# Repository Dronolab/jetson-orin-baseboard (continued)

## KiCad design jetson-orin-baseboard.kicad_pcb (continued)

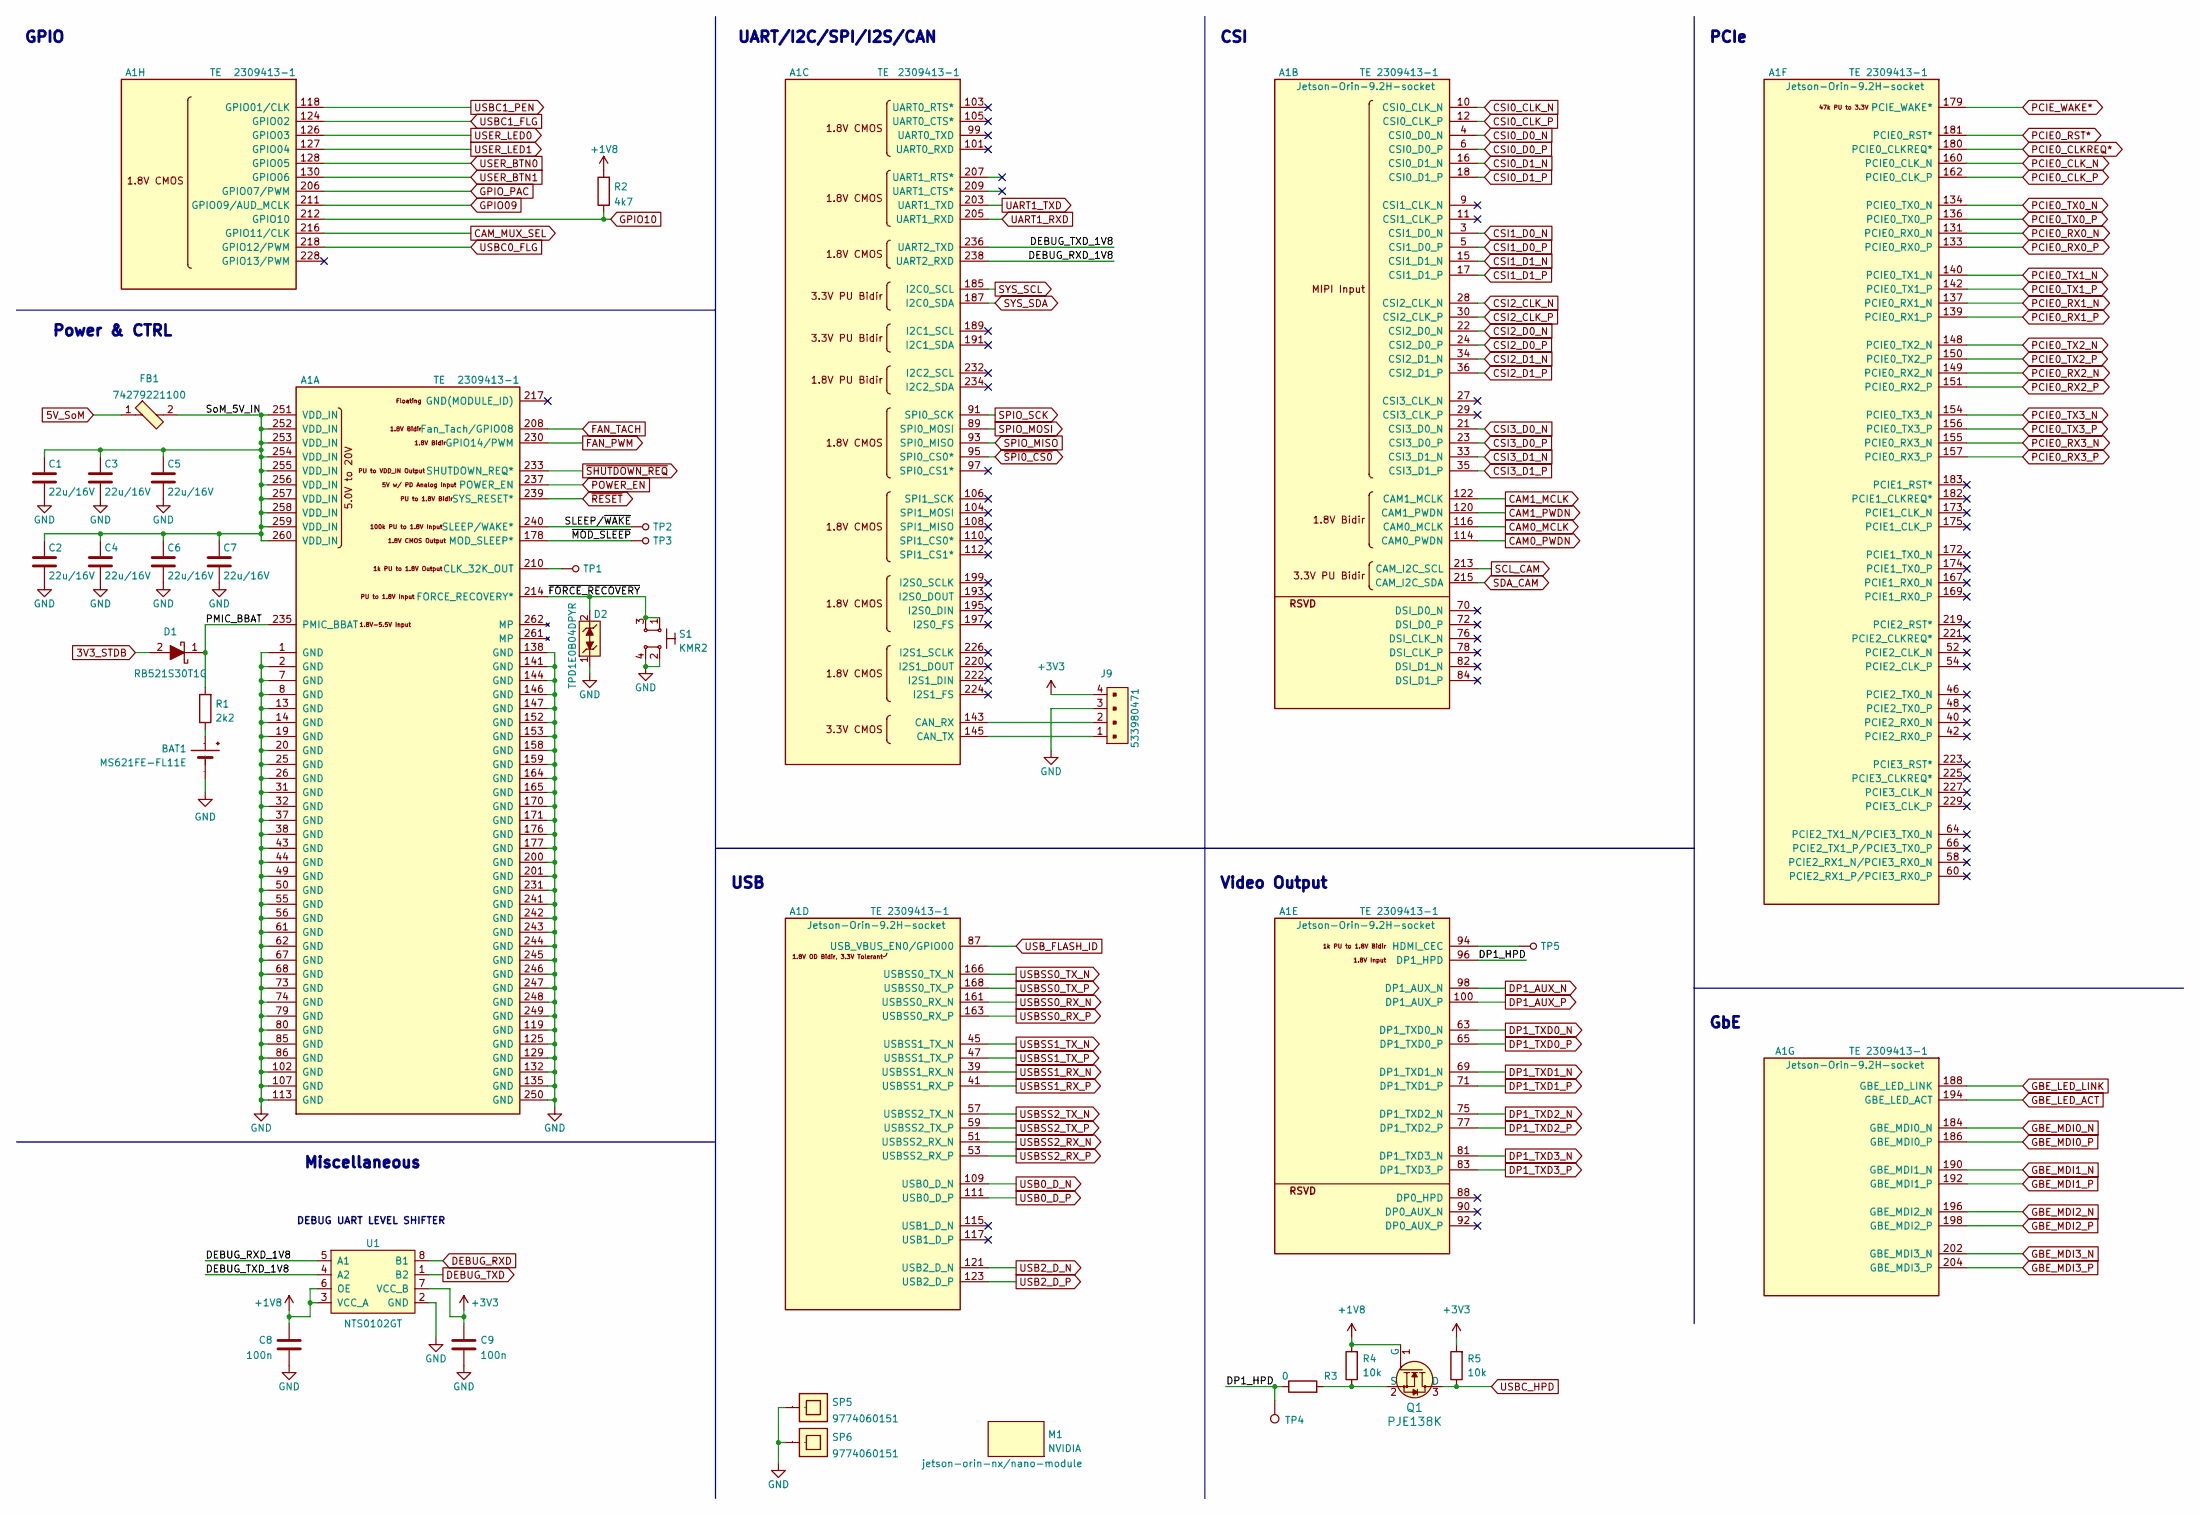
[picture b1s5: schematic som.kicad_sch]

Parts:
A1: Jetson-Orin-9.2H-socket; TE_2309413; MPN 2309413-1
BAT1: MS621FE-FL11E; MPN MS621FE-FL11E
C1, C2, C3, C4, C5, C6, C7: C_22u_0603_16V; 0603-cap; MPN CL10A226MO7JZNC
C8, C9: C_100n_0402; 0402-cap; MPN GRM155R61H104KE14D
D1: RB521S30T1G; SOD-523; MPN RB521S30T1G
D2: TPD1E0B04DPYR; XDFN-2_1x0.60mm; MPN TPD1E0B04DPYR
FB1: 74279221100; 1206-res; MPN 74279221100
J9: 533980471; Molex_PicoBlade_53398-0471_1x04-1MP_P1.25mm_Vertical; MPN 0533980471
M1: jetson-orin-nx/nano-module; jetson-orin-nx-nano-module
Q1: PJE138K; SOT-523; MPN PJE138K_R1_00001
R1: R_2k2_0402; 0402-res; MPN RC0402FR-072K2L
R2: R_4k7_0402; 0402-res; MPN MCS04020C4701FE000
R3: 0; 0402-res
R4, R5: 10k; 0402-res
S1: KMR2; SW_SPST_4.2x2.8; MPN KMR211NGLFS
SP5, SP6: 9774060151; MPN 9774060151
TP1, TP2, TP3, TP5: TP_SMD_0_75MM; Testpoint_smd_0_75mm
TP4: TestPoint; Testpoint_smd_0_75mm
U1: NTS0102GT; PSON50P100X195X50-8N; MPN NTS0102GT

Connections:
3V3_STDB: D1.2; also elsewhere on the board
5V_SoM: FB1.1; also elsewhere on the board
+1V8: C8.2, Q1.1 (G), R2.2, R4.2, U1.3 (VCC_A), U1.6 (OE); also elsewhere on the board
/SoM/DEBUG_RXD_1V8: A1.238 (UART2_RXD), U1.5 (A1)
/SoM/DEBUG_TXD_1V8: A1.236 (UART2_TXD), U1.4 (A2)
/SoM/DP1_HPD: A1.96 (DP1_HPD), R3.1, TP4.1
/SoM/PMIC_BBAT: A1.235 (PMIC_BBAT), D1.1, R1.2
/SoM/SLEEP/~WAKE: A1.240 (SLEEP/WAKE*), TP2.1
/SoM/SoM_5V_IN: A1.251 (VDD_IN), A1.252 (VDD_IN), A1.253 (VDD_IN), A1.254 (VDD_IN), A1.255 (VDD_IN), A1.256 (VDD_IN), A1.257 (VDD_IN), A1.258 (VDD_IN), A1.259 (VDD_IN), A1.260 (VDD_IN), C1.1, C2.1, C3.1, C4.1, C5.1, C6.1, C7.1, FB1.2
/SoM/~FORCE_RECOVERY: A1.214 (FORCE_RECOVERY*), D2.2, S1.1, S1.3
/SoM/~MOD_SLEEP: A1.178 (MOD_SLEEP*), TP3.1
CAM0_MCLK: A1.116 (CAM0_MCLK); also elsewhere on the board
CAM0_PWDN: A1.114 (CAM0_PWDN); also elsewhere on the board
CAM1_MCLK: A1.122 (CAM1_MCLK); also elsewhere on the board
CAM1_PWDN: A1.120 (CAM1_PWDN); also elsewhere on the board
CAM_MUX_SEL: A1.216 (GPIO11/CLK); also elsewhere on the board
CSI0_CLK_N: A1.10 (CSI0_CLK_N); also elsewhere on the board
CSI0_CLK_P: A1.12 (CSI0_CLK_P); also elsewhere on the board
CSI0_D0_N: A1.4 (CSI0_D0_N); also elsewhere on the board
CSI0_D0_P: A1.6 (CSI0_D0_P); also elsewhere on the board
CSI0_D1_N: A1.16 (CSI0_D1_N); also elsewhere on the board
CSI0_D1_P: A1.18 (CSI0_D1_P); also elsewhere on the board
CSI1_D0_N: A1.3 (CSI1_D0_N); also elsewhere on the board
CSI1_D0_P: A1.5 (CSI1_D0_P); also elsewhere on the board
CSI1_D1_N: A1.15 (CSI1_D1_N); also elsewhere on the board
CSI1_D1_P: A1.17 (CSI1_D1_P); also elsewhere on the board
CSI2_CLK_N: A1.28 (CSI2_CLK_N); also elsewhere on the board
CSI2_CLK_P: A1.30 (CSI2_CLK_P); also elsewhere on the board
CSI2_D0_N: A1.22 (CSI2_D0_N); also elsewhere on the board
CSI2_D0_P: A1.24 (CSI2_D0_P); also elsewhere on the board
CSI2_D1_N: A1.34 (CSI2_D1_N); also elsewhere on the board
CSI2_D1_P: A1.36 (CSI2_D1_P); also elsewhere on the board
CSI3_D0_N: A1.21 (CSI3_D0_N); also elsewhere on the board
CSI3_D0_P: A1.23 (CSI3_D0_P); also elsewhere on the board
CSI3_D1_N: A1.33 (CSI3_D1_N); also elsewhere on the board
CSI3_D1_P: A1.35 (CSI3_D1_P); also elsewhere on the board
DEBUG_RXD: U1.8 (B1); also elsewhere on the board
DEBUG_TXD: U1.1 (B2); also elsewhere on the board
DP1_AUX_N: A1.98 (DP1_AUX_N); also elsewhere on the board
DP1_AUX_P: A1.100 (DP1_AUX_P); also elsewhere on the board
DP1_TXD0_N: A1.63 (DP1_TXD0_N); also elsewhere on the board
DP1_TXD0_P: A1.65 (DP1_TXD0_P); also elsewhere on the board
DP1_TXD1_N: A1.69 (DP1_TXD1_N); also elsewhere on the board
DP1_TXD1_P: A1.71 (DP1_TXD1_P); also elsewhere on the board
DP1_TXD2_N: A1.75 (DP1_TXD2_N); also elsewhere on the board
DP1_TXD2_P: A1.77 (DP1_TXD2_P); also elsewhere on the board
DP1_TXD3_P: A1.83 (DP1_TXD3_P); also elsewhere on the board
FAN_PWM: A1.230 (GPIO14/PWM); also elsewhere on the board
FAN_TACH: A1.208 (Fan_Tach/GPIO08); also elsewhere on the board
GBE_LED_ACT: A1.194 (GBE_LED_ACT); also elsewhere on the board
GBE_LED_LINK: A1.188 (GBE_LED_LINK); also elsewhere on the board
GBE_MDI0_N: A1.184 (GBE_MDI0_N); also elsewhere on the board
GBE_MDI0_P: A1.186 (GBE_MDI0_P); also elsewhere on the board
GBE_MDI1_N: A1.190 (GBE_MDI1_N); also elsewhere on the board
GBE_MDI1_P: A1.192 (GBE_MDI1_P); also elsewhere on the board
GBE_MDI2_N: A1.196 (GBE_MDI2_N); also elsewhere on the board
GBE_MDI2_P: A1.198 (GBE_MDI2_P); also elsewhere on the board
GBE_MDI3_N: A1.202 (GBE_MDI3_N); also elsewhere on the board
GBE_MDI3_P: A1.204 (GBE_MDI3_P); also elsewhere on the board
GPIO09: A1.211 (GPIO09/AUD_MCLK); also elsewhere on the board
GPIO10: A1.212 (GPIO10), R2.1; also elsewhere on the board
unnamed: A1.210 (CLK_32K_OUT), TP1.1
unnamed: A1.94 (HDMI_CEC), TP5.1
unnamed: BAT1.+, R1.1
unnamed: Q1.2 (S), R3.2, R4.1
PCIE0_CLKREQ*: A1.180 (PCIE0_CLKREQ*); also elsewhere on the board
PCIE0_CLK_N: A1.160 (PCIE0_CLK_N); also elsewhere on the board
PCIE0_CLK_P: A1.162 (PCIE0_CLK_P); also elsewhere on the board
PCIE0_RST*: A1.181 (PCIE0_RST*); also elsewhere on the board
PCIE0_RX0_N: A1.131 (PCIE0_RX0_N); also elsewhere on the board
PCIE0_RX0_P: A1.133 (PCIE0_RX0_P); also elsewhere on the board
PCIE0_RX1_N: A1.137 (PCIE0_RX1_N); also elsewhere on the board
PCIE0_RX1_P: A1.139 (PCIE0_RX1_P); also elsewhere on the board
PCIE0_RX2_N: A1.149 (PCIE0_RX2_N); also elsewhere on the board
PCIE0_RX2_P: A1.151 (PCIE0_RX2_P); also elsewhere on the board
PCIE0_RX3_N: A1.155 (PCIE0_RX3_N); also elsewhere on the board
PCIE0_RX3_P: A1.157 (PCIE0_RX3_P); also elsewhere on the board
PCIE0_TX0_N: A1.134 (PCIE0_TX0_N); also elsewhere on the board
PCIE0_TX0_P: A1.136 (PCIE0_TX0_P); also elsewhere on the board
PCIE0_TX1_N: A1.140 (PCIE0_TX1_N); also elsewhere on the board
PCIE0_TX1_P: A1.142 (PCIE0_TX1_P); also elsewhere on the board
PCIE0_TX2_N: A1.148 (PCIE0_TX2_N); also elsewhere on the board
PCIE0_TX2_P: A1.150 (PCIE0_TX2_P); also elsewhere on the board
PCIE0_TX3_N: A1.154 (PCIE0_TX3_N); also elsewhere on the board
PCIE0_TX3_P: A1.156 (PCIE0_TX3_P); also elsewhere on the board
PCIE_WAKE*: A1.179 (PCIE_WAKE*); also elsewhere on the board
POWER_EN: A1.237 (POWER_EN); also elsewhere on the board
SCL_CAM: A1.213 (CAM_I2C_SCL); also elsewhere on the board
SDA_CAM: A1.215 (CAM_I2C_SDA); also elsewhere on the board
SPIO_MISO: A1.93 (SPI0_MISO); also elsewhere on the board
SPIO_MOSI: A1.89 (SPI0_MOSI); also elsewhere on the board
SPIO_SCK: A1.91 (SPI0_SCK); also elsewhere on the board
SYS_SCL: A1.185 (I2C0_SCL); also elsewhere on the board
SYS_SDA: A1.187 (I2C0_SDA); also elsewhere on the board
USB0_D_N: A1.109 (USB0_D_N); also elsewhere on the board
USB0_D_P: A1.111 (USB0_D_P); also elsewhere on the board
USB2_D_N: A1.121 (USB2_D_N); also elsewhere on the board
USB2_D_P: A1.123 (USB2_D_P); also elsewhere on the board
USBC0_FLG: A1.218 (GPIO12/PWM); also elsewhere on the board
USBC1_FLG: A1.124 (GPIO02); also elsewhere on the board
USBC1_PEN: A1.118 (GPIO01/CLK); also elsewhere on the board
USBC_HPD: Q1.3 (D), R5.1; also elsewhere on the board
USBSS0_RX_N: A1.161 (USBSS0_RX_N); also elsewhere on the board
USBSS0_RX_P: A1.163 (USBSS0_RX_P); also elsewhere on the board
USBSS0_TX_N: A1.166 (USBSS0_TX_N); also elsewhere on the board
USBSS0_TX_P: A1.168 (USBSS0_TX_P); also elsewhere on the board
USBSS1_RX_N: A1.39 (USBSS1_RX_N); also elsewhere on the board
USBSS1_RX_P: A1.41 (USBSS1_RX_P); also elsewhere on the board
USBSS1_TX_N: A1.45 (USBSS1_TX_N); also elsewhere on the board
USBSS1_TX_P: A1.47 (USBSS1_TX_P); also elsewhere on the board
USBSS2_RX_N: A1.51 (USBSS2_RX_N); also elsewhere on the board
USBSS2_RX_P: A1.53 (USBSS2_RX_P); also elsewhere on the board
USBSS2_TX_N: A1.57 (USBSS2_TX_N); also elsewhere on the board
USBSS2_TX_P: A1.59 (USBSS2_TX_P); also elsewhere on the board
USB_FLASH_ID: A1.87 (USB_VBUS_EN0/GPIO00); also elsewhere on the board
USER_BTN0: A1.128 (GPIO05); also elsewhere on the board
USER_BTN1: A1.130 (GPIO06); also elsewhere on the board
USER_LED0: A1.126 (GPIO03); also elsewhere on the board
USER_LED1: A1.127 (GPIO04); also elsewhere on the board
~RESET: A1.239 (SYS_RESET*); also elsewhere on the board
~SHUTDOWN_REQ: A1.233 (SHUTDOWN_REQ*); also elsewhere on the board
~SPI0_CS0: A1.95 (SPI0_CS0*); also elsewhere on the board

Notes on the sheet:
DEBUG UART LEVEL SHIFTER
CSI
Video Output
Power & CTRL
UART/I2C/SPI/I2S/CAN
PCIe
GbE
USB
GPIO
Miscellaneous

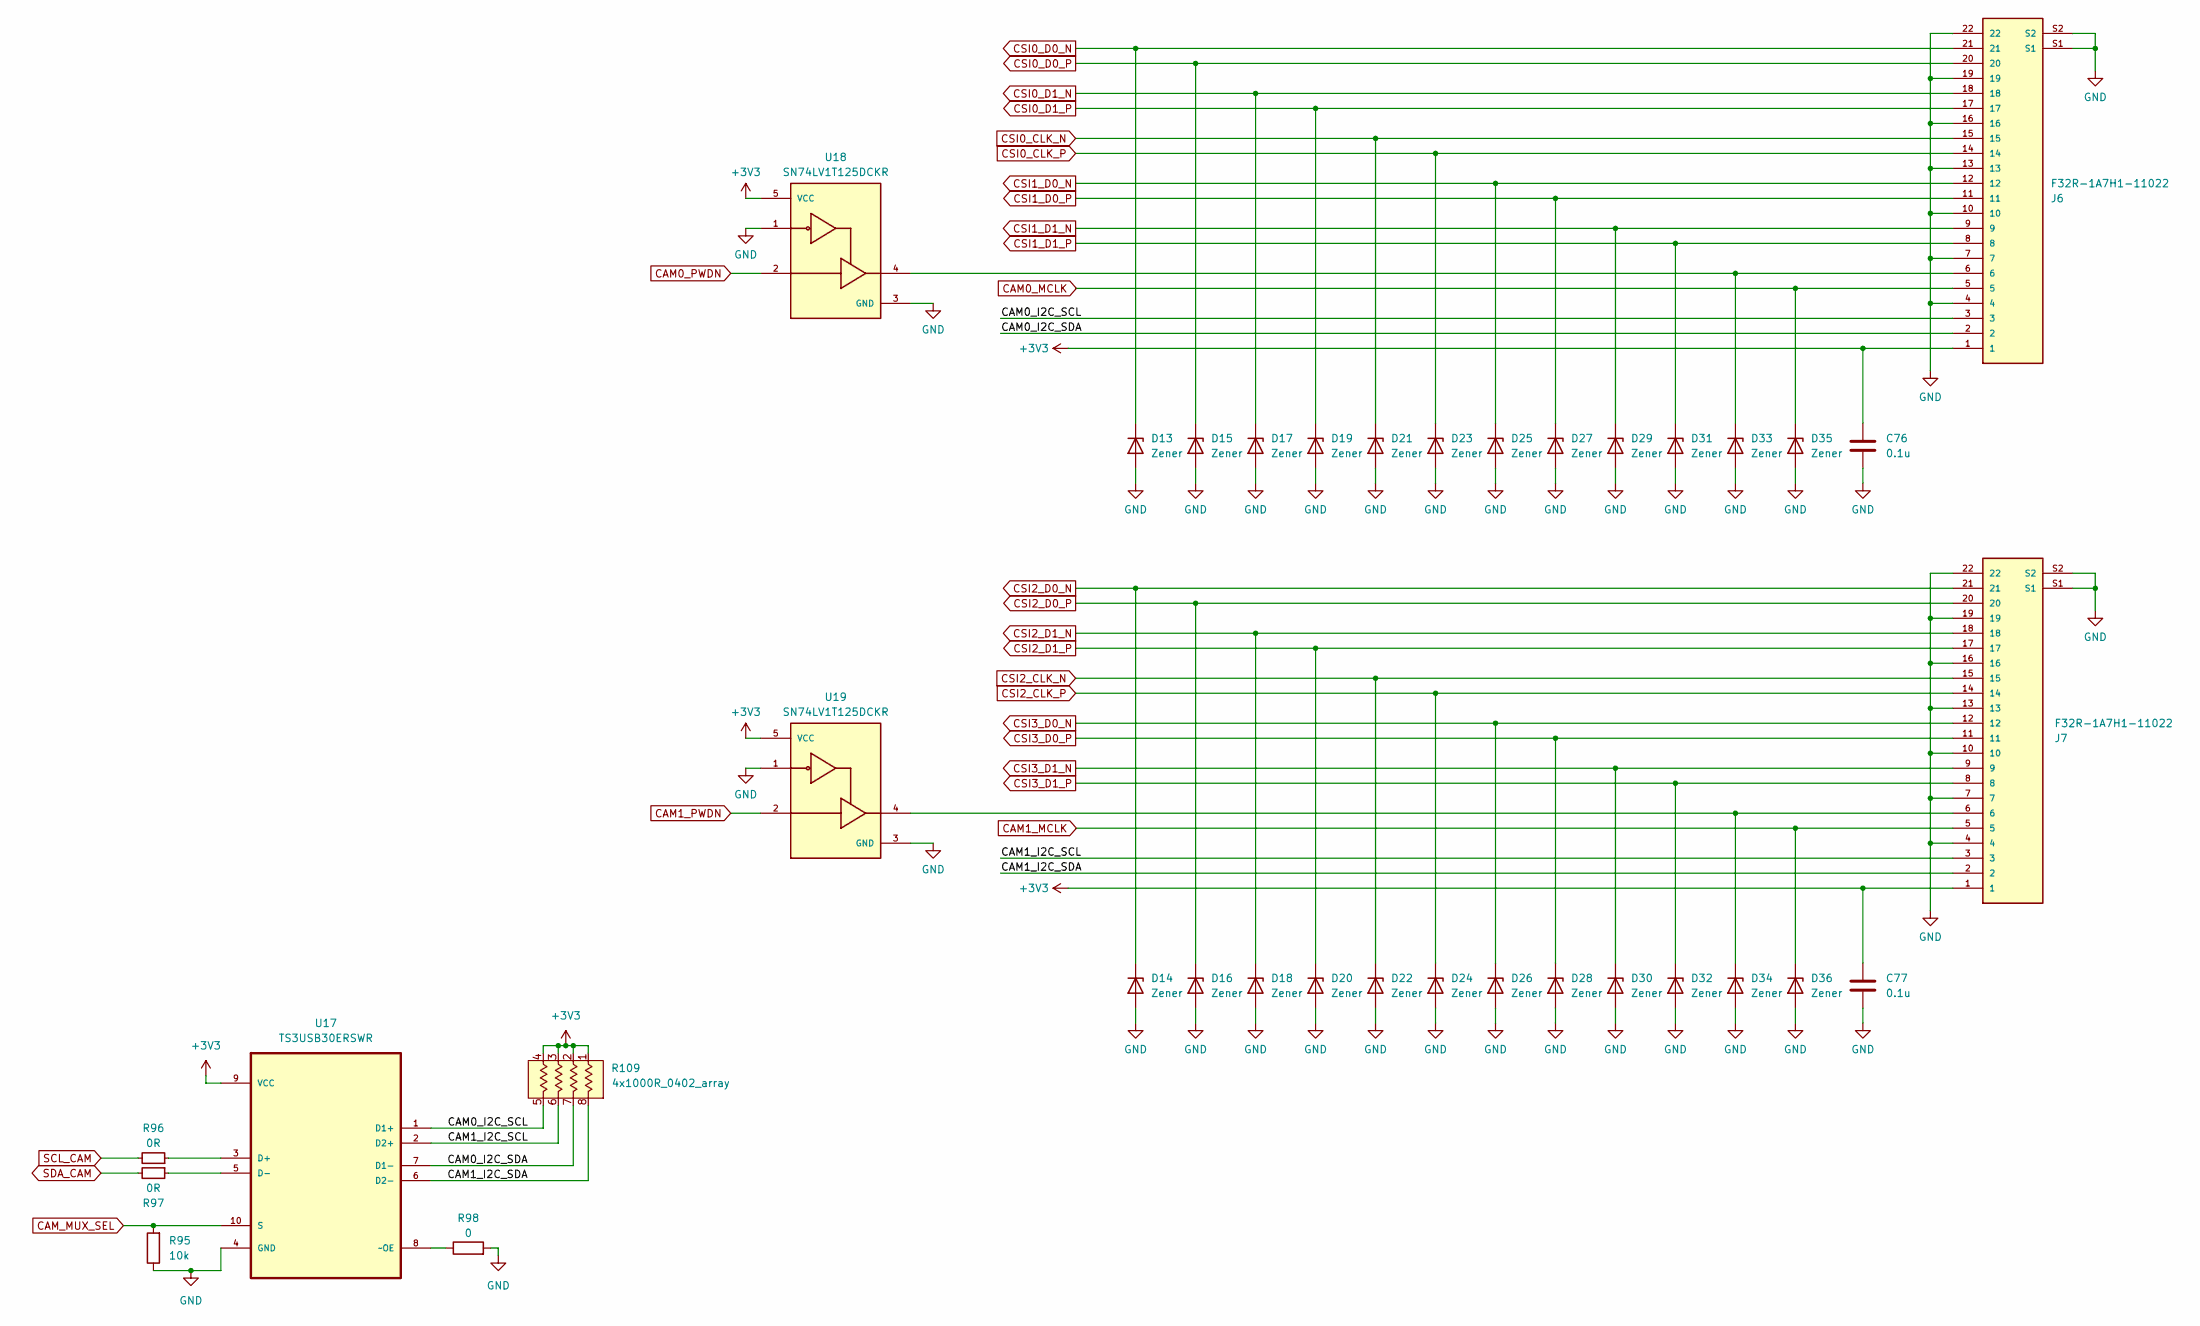
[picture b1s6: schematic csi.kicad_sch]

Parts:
C76, C77: 0.1u; 0402-cap
D13, D14, D15, D16, D17, D18, D19, D20, D21, D22, D23, D24, D25, D26, D27, D28, D29, D30, D31, D32, D33, D34, D35, D36: Zener; DFN1006-2
J6, J7: F32R-1A7H1-11022; AMPHENOL_F32R-1A7H1-11022; PARTREV C
R95: 10k; 0402-res
R96, R97: R_0R_0402; 0402-res; MPN ERJ2GE0R00X
R98: 0; 0402-res
R109: 4x1000R_0402_array; R_Array_4x0402; MPN EXB-28V331JX
U17: TS3USB30ERSWR; QFN40P140X180X55-10N; MPN TS3USB30ERSWR
U18, U19: SN74LV1T125DCKR; SOT65P210X110-5N; PARTREV A

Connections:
/Cameras/CAM1_I2C_SDA: J7.2, R109.8, U17.6 (D2-); also elsewhere on the board
CAM0_MCLK: D35.K, J6.5; also elsewhere on the board
CAM0_PWDN: U18.2; also elsewhere on the board
CAM1_MCLK: D36.K, J7.5; also elsewhere on the board
CAM1_PWDN: U19.2; also elsewhere on the board
CAM_MUX_SEL: R95.2, U17.10 (S); also elsewhere on the board
CSI0_CLK_N: D21.K, J6.15; also elsewhere on the board
CSI0_CLK_P: D23.K, J6.14; also elsewhere on the board
CSI0_D0_N: D13.K, J6.21; also elsewhere on the board
CSI0_D0_P: D15.K, J6.20; also elsewhere on the board
CSI0_D1_N: D17.K, J6.18; also elsewhere on the board
CSI0_D1_P: D19.K, J6.17; also elsewhere on the board
CSI1_D0_N: D25.K, J6.12; also elsewhere on the board
CSI1_D0_P: D27.K, J6.11; also elsewhere on the board
CSI1_D1_N: D29.K, J6.9; also elsewhere on the board
CSI1_D1_P: D31.K, J6.8; also elsewhere on the board
CSI2_CLK_N: D22.K, J7.15; also elsewhere on the board
CSI2_CLK_P: D24.K, J7.14; also elsewhere on the board
CSI2_D0_N: D14.K, J7.21; also elsewhere on the board
CSI2_D0_P: D16.K, J7.20; also elsewhere on the board
CSI2_D1_N: D18.K, J7.18; also elsewhere on the board
CSI2_D1_P: D20.K, J7.17; also elsewhere on the board
CSI3_D0_N: D26.K, J7.12; also elsewhere on the board
CSI3_D0_P: D28.K, J7.11; also elsewhere on the board
CSI3_D1_N: D30.K, J7.9; also elsewhere on the board
CSI3_D1_P: D32.K, J7.8; also elsewhere on the board
unnamed: D33.K, J6.6, U18.4
unnamed: D34.K, J7.6, U19.4
unnamed: R96.1, U17.3 (D+)
unnamed: R97.1, U17.5 (D-)
unnamed: R98.1, U17.8 (~OE)
SCL_CAM: R96.2; also elsewhere on the board
SDA_CAM: R97.2; also elsewhere on the board

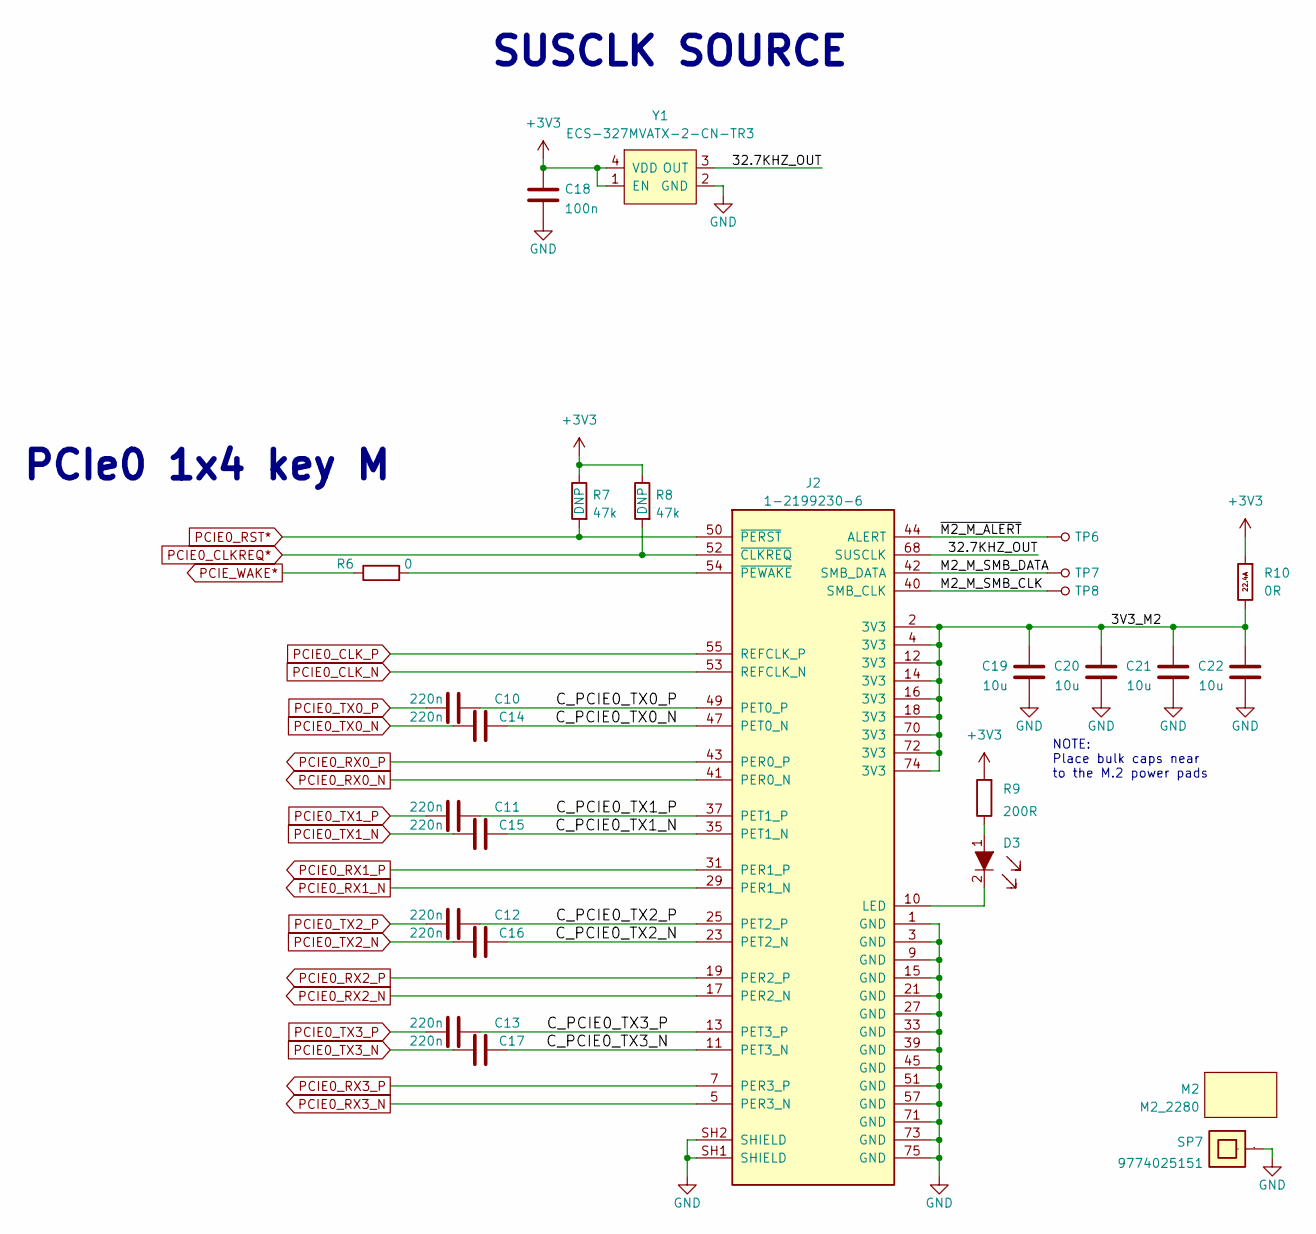
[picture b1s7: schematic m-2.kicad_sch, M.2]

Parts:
C10, C11, C12, C13, C14, C15, C16, C17: C_220n_0402; 0402-cap; MPN CC0402KRX5R6BB224
C18: C_100n_0402; 0402-cap; MPN GRM155R61H104KE14D
C19, C20, C21, C22: C_10u_0603; 0603-cap; MPN GRM188R61A106KE69D
D3: LTST-C190GKT; LED_0603; MPN LTST-C190GKT
J2: 1-2199230-6; MPN 1-2199230-6
M2: M2_2280; m2_2280
R6: 0; 0402-res
R7, R8: R_47k_0402; 0402-res; MPN MCMR04X4702FTL
R9: R_200R_0402; 0402-res; MPN RC0402FR-07200RL
R10: R_0R_0603_HPWR; 0603-res; MPN PMR03EZPJ000
SP7: 9774025151; MPN 9774025151
TP6, TP7, TP8: TP_SMD_0_75MM; Testpoint_smd_0_75mm
Y1: ECS-327MVATX-2-CN-TR3; Oscillator_SMD_ECS_2520MV-xxx-xx-4Pin_2.5x2.0mm; MPN ECS-327MVATX-2-CN-TR3

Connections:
/M.2/3V3_M2: C19.1, C20.1, C21.1, C22.1, J2.2 (3V3), J2.4 (3V3), J2.12 (3V3), J2.14 (3V3), J2.16 (3V3), J2.18 (3V3), J2.70 (3V3), J2.72 (3V3), J2.74 (3V3), R10.1
/M.2/32.7KHZ_OUT: J2.68 (SUSCLK), Y1.3 (OUT)
/M.2/C_PCIE0_TX0_N: C14.2, J2.47 (PET0_N)
/M.2/C_PCIE0_TX0_P: C10.2, J2.49 (PET0_P)
/M.2/C_PCIE0_TX1_N: C15.2, J2.35 (PET1_N)
/M.2/C_PCIE0_TX1_P: C11.2, J2.37 (PET1_P)
/M.2/C_PCIE0_TX2_N: C16.2, J2.23 (PET2_N)
/M.2/C_PCIE0_TX2_P: C12.2, J2.25 (PET2_P)
/M.2/C_PCIE0_TX3_N: C17.2, J2.11 (PET3_N)
/M.2/C_PCIE0_TX3_P: C13.2, J2.13 (PET3_P)
/M.2/M2_M_SMB_CLK: J2.40 (SMB_CLK), TP8.1
/M.2/M2_M_SMB_DATA: J2.42 (SMB_DATA), TP7.1
/M.2/~M2_M_ALERT: J2.44 (ALERT), TP6.1
unnamed: D3.1, R9.1
unnamed: D3.2, J2.10 (LED)
unnamed: J2.54 (~PEWAKE), R6.2
PCIE0_CLKREQ*: J2.52 (~CLKREQ), R8.2; also elsewhere on the board
PCIE0_CLK_N: J2.53 (REFCLK_N); also elsewhere on the board
PCIE0_CLK_P: J2.55 (REFCLK_P); also elsewhere on the board
PCIE0_RST*: J2.50 (~PERST), R7.2; also elsewhere on the board
PCIE0_RX0_N: J2.41 (PER0_N); also elsewhere on the board
PCIE0_RX0_P: J2.43 (PER0_P); also elsewhere on the board
PCIE0_RX1_N: J2.29 (PER1_N); also elsewhere on the board
PCIE0_RX1_P: J2.31 (PER1_P); also elsewhere on the board
PCIE0_RX2_N: J2.17 (PER2_N); also elsewhere on the board
PCIE0_RX2_P: J2.19 (PER2_P); also elsewhere on the board
PCIE0_RX3_N: J2.5 (PER3_N); also elsewhere on the board
PCIE0_RX3_P: J2.7 (PER3_P); also elsewhere on the board
PCIE0_TX0_N: C14.1; also elsewhere on the board
PCIE0_TX0_P: C10.1; also elsewhere on the board
PCIE0_TX1_N: C15.1; also elsewhere on the board
PCIE0_TX1_P: C11.1; also elsewhere on the board
PCIE0_TX2_N: C16.1; also elsewhere on the board
PCIE0_TX2_P: C12.1; also elsewhere on the board
PCIE0_TX3_N: C17.1; also elsewhere on the board
PCIE0_TX3_P: C13.1; also elsewhere on the board
PCIE_WAKE*: R6.1; also elsewhere on the board

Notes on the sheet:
PCIe0 1x4 key M
NOTE: Place bulk caps near to the M.2 power pads
SUSCLK SOURCE

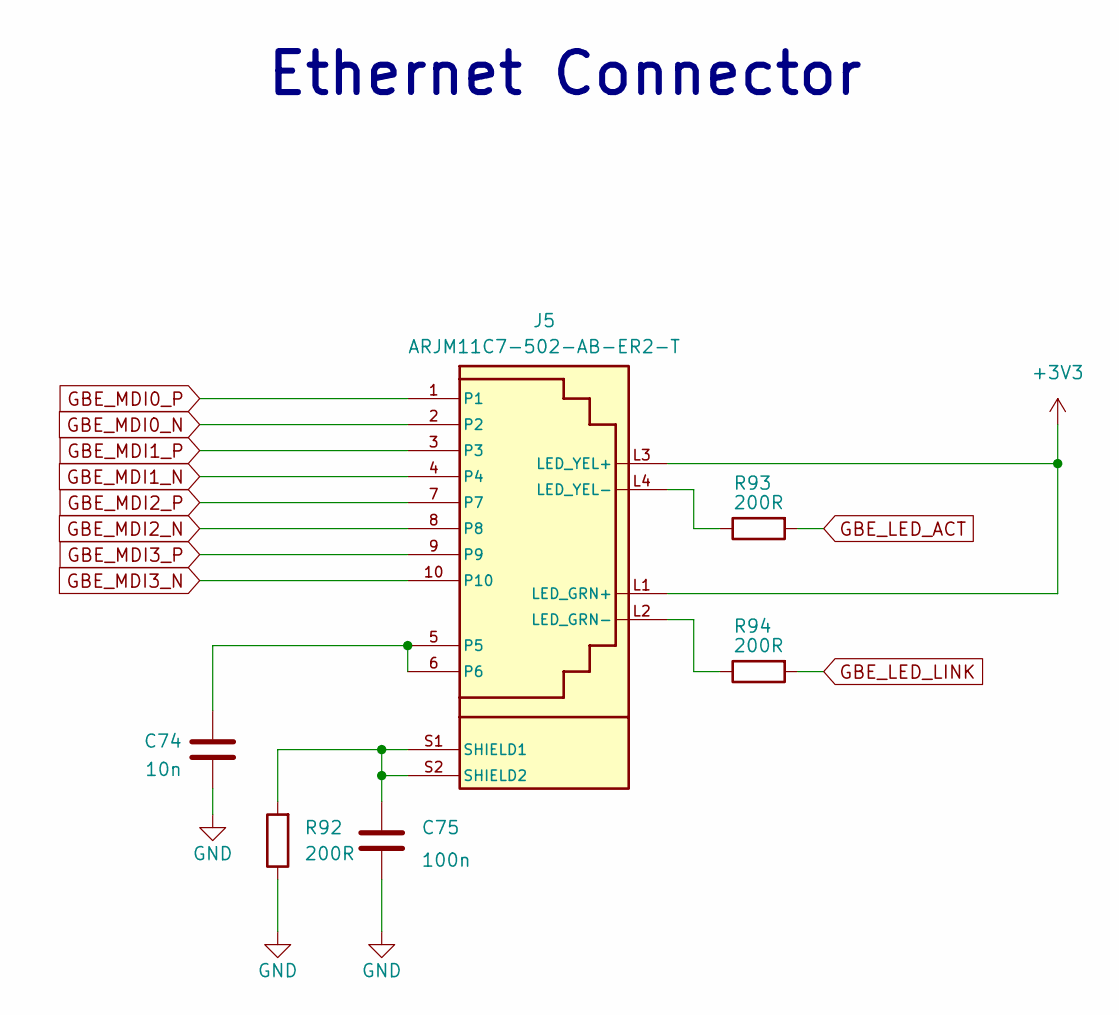
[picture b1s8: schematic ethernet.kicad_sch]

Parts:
C74: C_10n_0402; 0402-cap; MPN 04025G103ZAT2A
C75: C_100n_0402; 0402-cap; MPN GRM155R61H104KE14D
J5: ARJM11C7-502-AB-ER2-T; ABRACON_ARJM11C7-502-AB-ER2-T; MPN ARJM11C7-502-AB-ER2-T
R92, R93, R94: R_200R_0402; 0402-res; MPN RC0402FR-07200RL

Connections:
GBE_LED_ACT: R93.2; also elsewhere on the board
GBE_LED_LINK: R94.2; also elsewhere on the board
GBE_MDI0_N: J5.2; also elsewhere on the board
GBE_MDI0_P: J5.1; also elsewhere on the board
GBE_MDI1_N: J5.4; also elsewhere on the board
GBE_MDI1_P: J5.3; also elsewhere on the board
GBE_MDI2_N: J5.8; also elsewhere on the board
GBE_MDI2_P: J5.7; also elsewhere on the board
GBE_MDI3_N: J5.10; also elsewhere on the board
GBE_MDI3_P: J5.9; also elsewhere on the board
unnamed: J5.L2 (LED_GRN-), R94.1
unnamed: J5.L4 (LED_YEL-), R93.1
unnamed: C74.1, J5.5, J5.6
unnamed: C75.1, J5.S1 (SHIELD1), J5.S2 (SHIELD2), R92.2

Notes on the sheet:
Ethernet Connector

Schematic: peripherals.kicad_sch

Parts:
C78, C80: C_100n_0402; 0402-cap; MPN GRM155R61H104KE14D
C79: 0.1u; 0402-cap
C81: 2.2u; 0402-cap
C82: 10n; 0402-cap
C83: 0.47u; 0402-cap
C84, C85, C86, C88: C_1u_0402; 0402-cap; MPN C1005X6S1A105K050BC
C87, C89: 100n; 0402-cap
D37, D38: LTST-C190GKT; LED_0603; MPN LTST-C190GKT
D39, D40, D41, D42, D43, D44: TPD1E0B04DPYR; XDFN-2_1x0.60mm; MPN TPD1E0B04DPYR
J8: TC2050-IDC-NL; TC2050-IDC-NL_2x05_Vertical; MPN TC2050-IDC-NL
J9: 533980471; Molex_PicoBlade_53398-0471_1x04-1MP_P1.25mm_Vertical; MPN 0533980471
J10: 532611071; MOLEX_532611071; PARTREV J
J11: ERF8-020-05.0-S-DV-L-TR; SAMTEC_ERF8-020-05.0-S-DV-L-TR
Q4, Q5: PJE138K; SOT-523; MPN PJE138K_R1_00001
R103, R104, R117, R118: R_0R_0402; 0402-res; MPN ERJ2GE0R00X
R105: 4x0R_0201_array; EXB18V; MPN EXB-18VR000X
R106: 0; 0402-res
R107, R110: R_100k_0402; 0402-res; MPN CRCW0402100KFKEDHP
R108, R111: R_200R_0402; 0402-res; MPN RC0402FR-07200RL
R109: 4x330R_0402_array; R_Array_4x0402; MPN EXB-28V331JX
R112, R113: R_10k_0402; 0402-res; MPN CRCW040210K0FKEDHP
R114, R115, R116, R119: R_0R_0603; 0603-res; MPN CR0603-J/-000ELF
S2, S3: KMR2; SW_SPST_4.2x2.8; MPN KMR211NGLFS
U20: NTS0102GT; PSON50P100X195X50-8N; MPN NTS0102GT
U21: ICM-20602; LGA-16_3x3mm_P0.5mm_LayoutBorder3x5y

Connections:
+1V8: C78.2, C79.1, C81.1, R112.2, R113.2, R115.2, U20.3 (VCC_A), U20.6 (OE), U21.16 (VDD); also elsewhere on the board
+12V: R119.1
/Cameras/CAM1_I2C_SDA: R109.8; also elsewhere on the board
/Peripherals/1V8_CONN: C85.1, J11.02, J11.04, R115.1
/Peripherals/3V3_CONN: C84.1, J11.33, J11.35, J11.37, R114.1
/Peripherals/5V_CONN: C86.1, J11.01, J11.03, J11.05, J11.07, R116.2
/Peripherals/12V_CONN: C88.1, J11.32, J11.34, J11.36, J11.38, R119.2
/Peripherals/FC_RX: J10.3, J11.16
/Peripherals/FC_TX: J10.2, J11.14
/Peripherals/IO1: J10.5, J11.13
/Peripherals/IO2: J10.6, J11.11
/Peripherals/IO3: J10.7, J11.15
/Peripherals/IO4: J10.9, J11.08
/Peripherals/IO5: J10.10, J11.10
/Peripherals/USBSS1_TX_N_CONN: C89.1, D44.1, J11.22
/Peripherals/USBSS1_TX_P_CONN: C87.1, D43.1, J11.20
EEPROM_PWR: J8.1; also elsewhere on the board
FAN_PWM: U20.5 (A1); also elsewhere on the board
FAN_TACH: U20.4 (A2); also elsewhere on the board
GPIO09: R106.2; also elsewhere on the board
unnamed: D37.1, R108.1
unnamed: D38.1, R111.1
unnamed: J8.3, R103.1
unnamed: J8.4, R104.1
unnamed: J8.7, R105.4
unnamed: J8.8, R105.3
unnamed: J8.9, R105.2
unnamed: J8.10, R105.1
unnamed: J11.27, R117.2
unnamed: J11.29, R118.2
unnamed: D37.2, Q4.3 (D)
unnamed: D38.2, Q5.3 (D)
unnamed: R106.1, U21.6 (INT)
unnamed: C83.1, U21.14 (REGOUT)
unnamed: C82.1, U21.1 (VDDIO)
PDC_MISO: R105.6; also elsewhere on the board
PDC_MOSI: R105.5; also elsewhere on the board
PDC_SCLK: R105.7; also elsewhere on the board
SPIO_MISO: U21.4 (SAO/SD0); also elsewhere on the board
SPIO_MOSI: U21.3 (SDA/SDI); also elsewhere on the board
SPIO_SCK: U21.2 (SCL/SPC); also elsewhere on the board
SYS_SCL: R104.2, R118.1; also elsewhere on the board
SYS_SDA: R103.2, R117.1; also elsewhere on the board
USBSS1_RX_N: D41.1, J11.28; also elsewhere on the board
USBSS1_RX_P: D42.1, J11.26; also elsewhere on the board
USBSS1_TX_N: C89.2; also elsewhere on the board
USBSS1_TX_P: C87.2; also elsewhere on the board
USER_BTN0: D39.2, R112.1, S2.1, S2.3; also elsewhere on the board
USER_BTN1: D40.2, R113.1, S3.1, S3.3; also elsewhere on the board
USER_LED0: Q4.1 (G), R107.2; also elsewhere on the board
USER_LED1: Q5.1 (G), R110.2; also elsewhere on the board
~PDC_CS: R105.8; also elsewhere on the board
~SPI0_CS0: U21.5 (~CS); also elsewhere on the board

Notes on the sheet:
pinout compatible with www.github.com/antmicro/ftdi-toolkit
Fan connector
Expansion connector
LED indicators
Expansion connector resistors
Flight Controller Connector
Debug connector
SYS I2C Addresses in Use -0100011 for Port 1 of I2C1 of TPS65988 (CONFIGURABLE) -0100111 for Port 2 of I2C1 of TPS65988 (CONFIGURABLE) -0010010 for TUSB1046-DCI (I2C UNUSED, CONFIGURABLE) -1X00111 for HD3SS3220(I2C UNUSED, 2 CHOICE) -010000X for planned PCAL6408A on PAC PCB (2 CHOICE) -1000000 for 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
Buttons
IMU

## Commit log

2023-07-05 Renaming Sheets
2023-07-06 PCIE Simplification finished
2023-07-07 Simplification continues
2023-07-07 Project saving and real commit
2023-07-08 Changed Ethernet Connector
2023-07-08 New Gitignore
2023-07-08 Change gitignore
2023-07-08 Gitignore change
2023-07-08 Caps and DP to USBC HPD
2023-07-08 Added things left to do list
2023-07-09 Added IMU + MICROPHONES
2023-07-10 Add 4G Sheet
2023-07-10 Adding 4G M.2 B
2023-07-10 4G V1 Done
2023-07-19 Buzzer ajouté
2023-07-19 Updated list of things to do
2023-08-24 Changes to CSI for multiplexing and to peripherals for better PAC connector
2023-08-24 Little change
2023-08-24 little changes that day
2023-10-04 Réduction des pins pour le payload
    Voici ce que j'ai conservé:
    -6 IO
    -Communication CAN du skymate
    -Mémoire flash pour serial (SYS_SDA/SYS_SCL)
    -Communication serial (I2C2)
    -Alimentation 3V3 5V 12V
2023-10-11 changement vers gmsl2 en cours
2023-10-17 Reducing pin count to 30
2023-10-23 Schematic check
    Include Pinmux and Schematic Check excels in doc folder and doing a lot of checking and correcting things.
2023-10-24 Small changes
2023-10-25 Schematic Done
2023-10-27 Schematic V1 and footprints assigned
2023-10-27 New PCB with errors
2023-10-27 Footprints well assigned, XT30 added, Shields grounded
2023-11-21 Starting PCB Design
2023-11-22 Resetting PCB
2023-11-23 Camera interface placement
2023-11-26 Edge Cuts & Holes setup like original Antmicro Jetson Orin Baseboard
2023-11-26 Text size changes and positioning important components part 1
2023-11-27 Ajustement placement interface camera et RJ45 port
2023-11-29 Putting SSD right place and buck component placements
2023-11-29 Copiage de placement composantes part 2
2023-12-02 copying positions part 4
2023-12-08 Adding a no connect and removing a test point on hdmi_cec
